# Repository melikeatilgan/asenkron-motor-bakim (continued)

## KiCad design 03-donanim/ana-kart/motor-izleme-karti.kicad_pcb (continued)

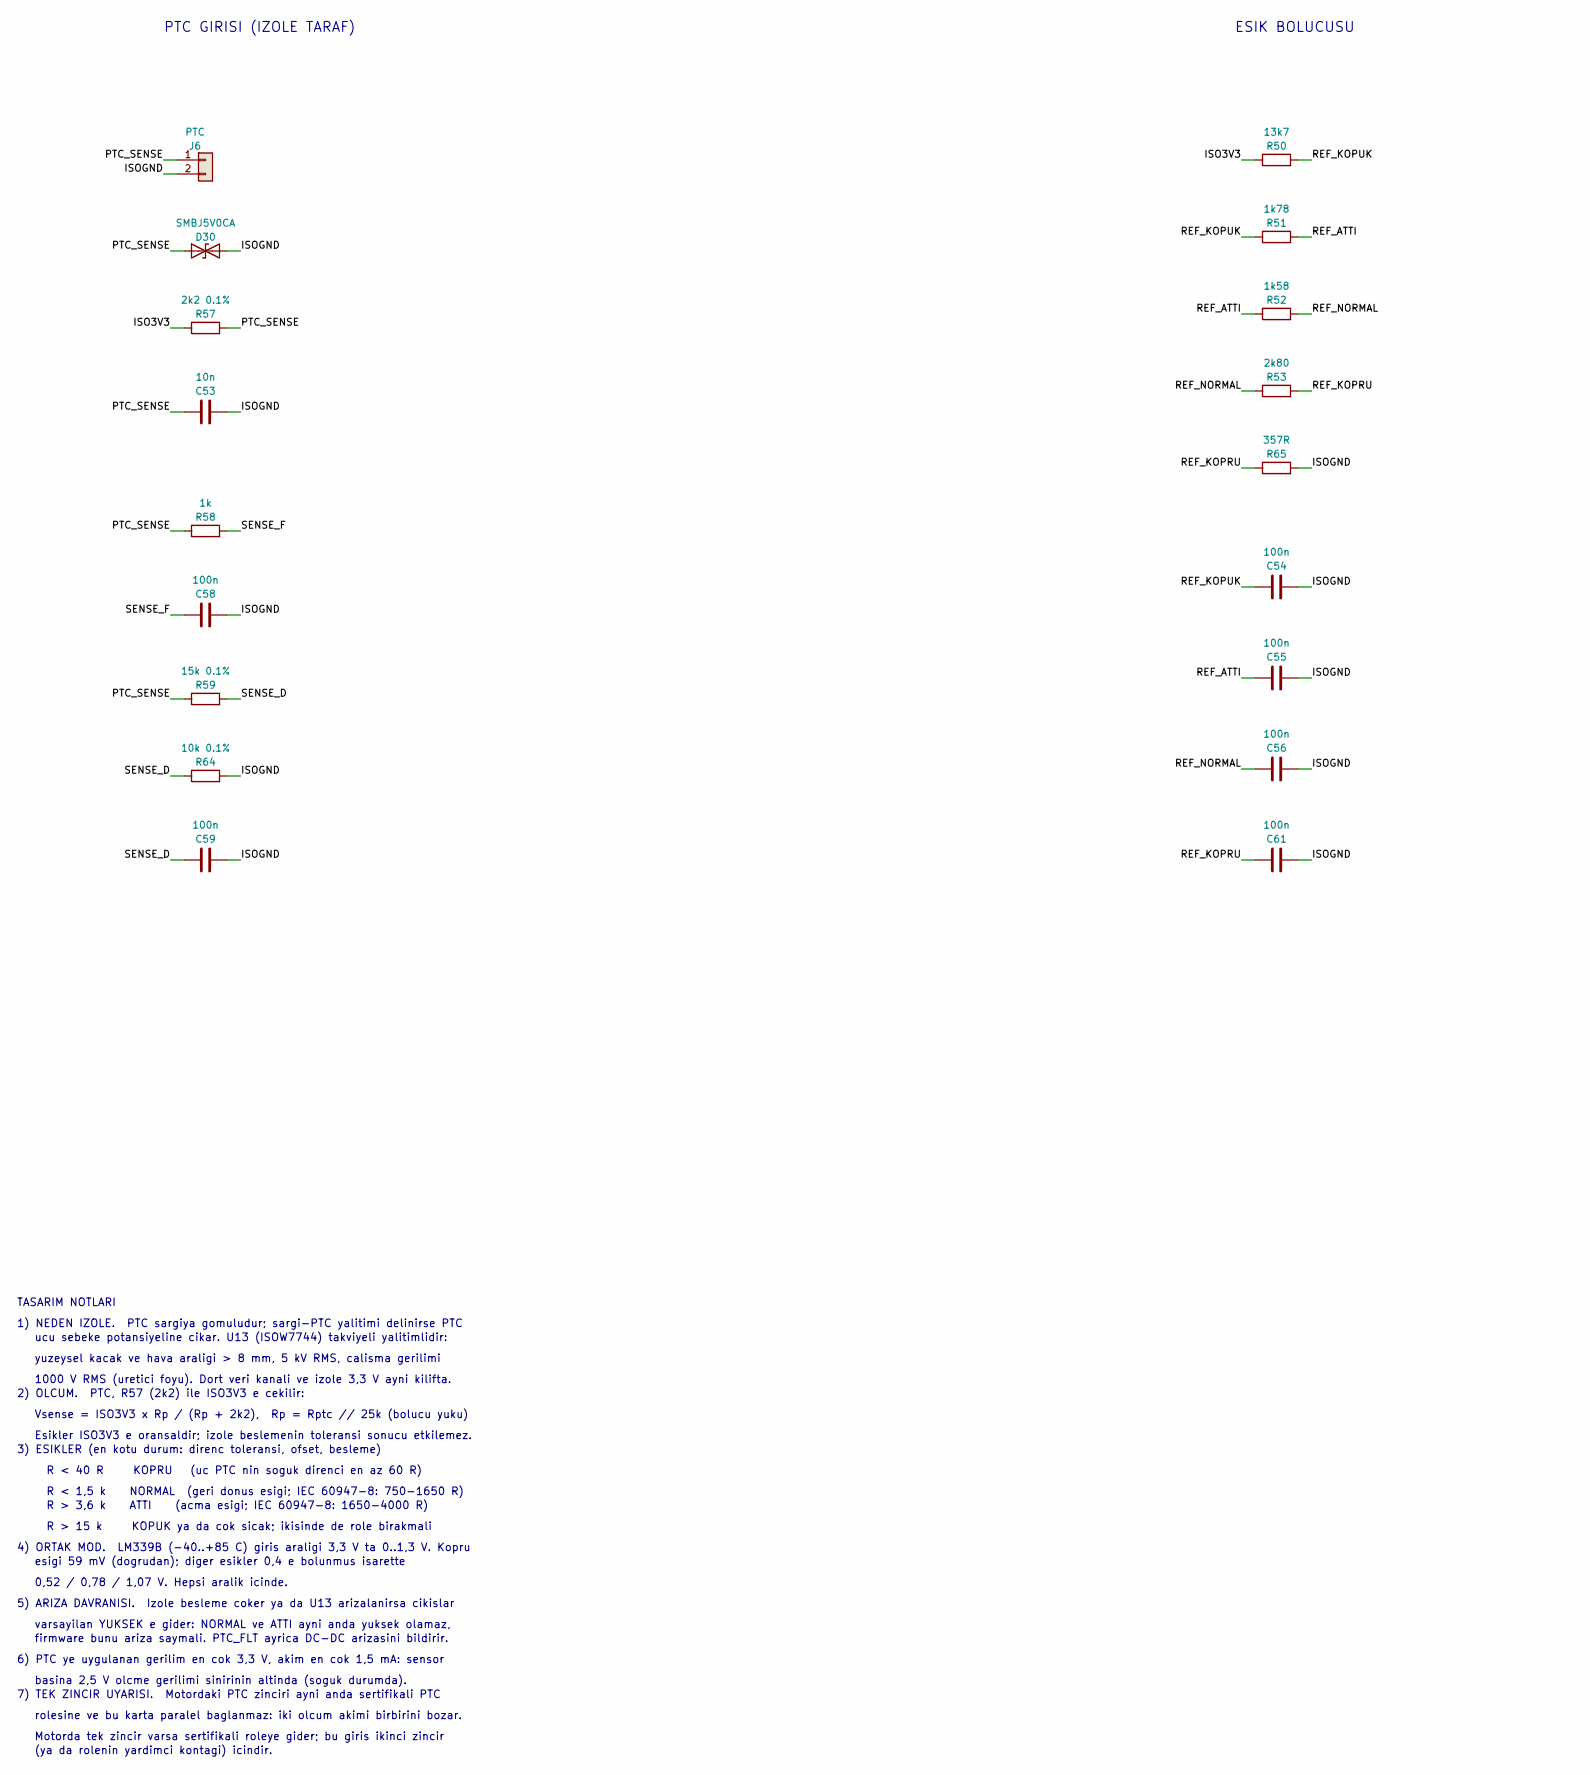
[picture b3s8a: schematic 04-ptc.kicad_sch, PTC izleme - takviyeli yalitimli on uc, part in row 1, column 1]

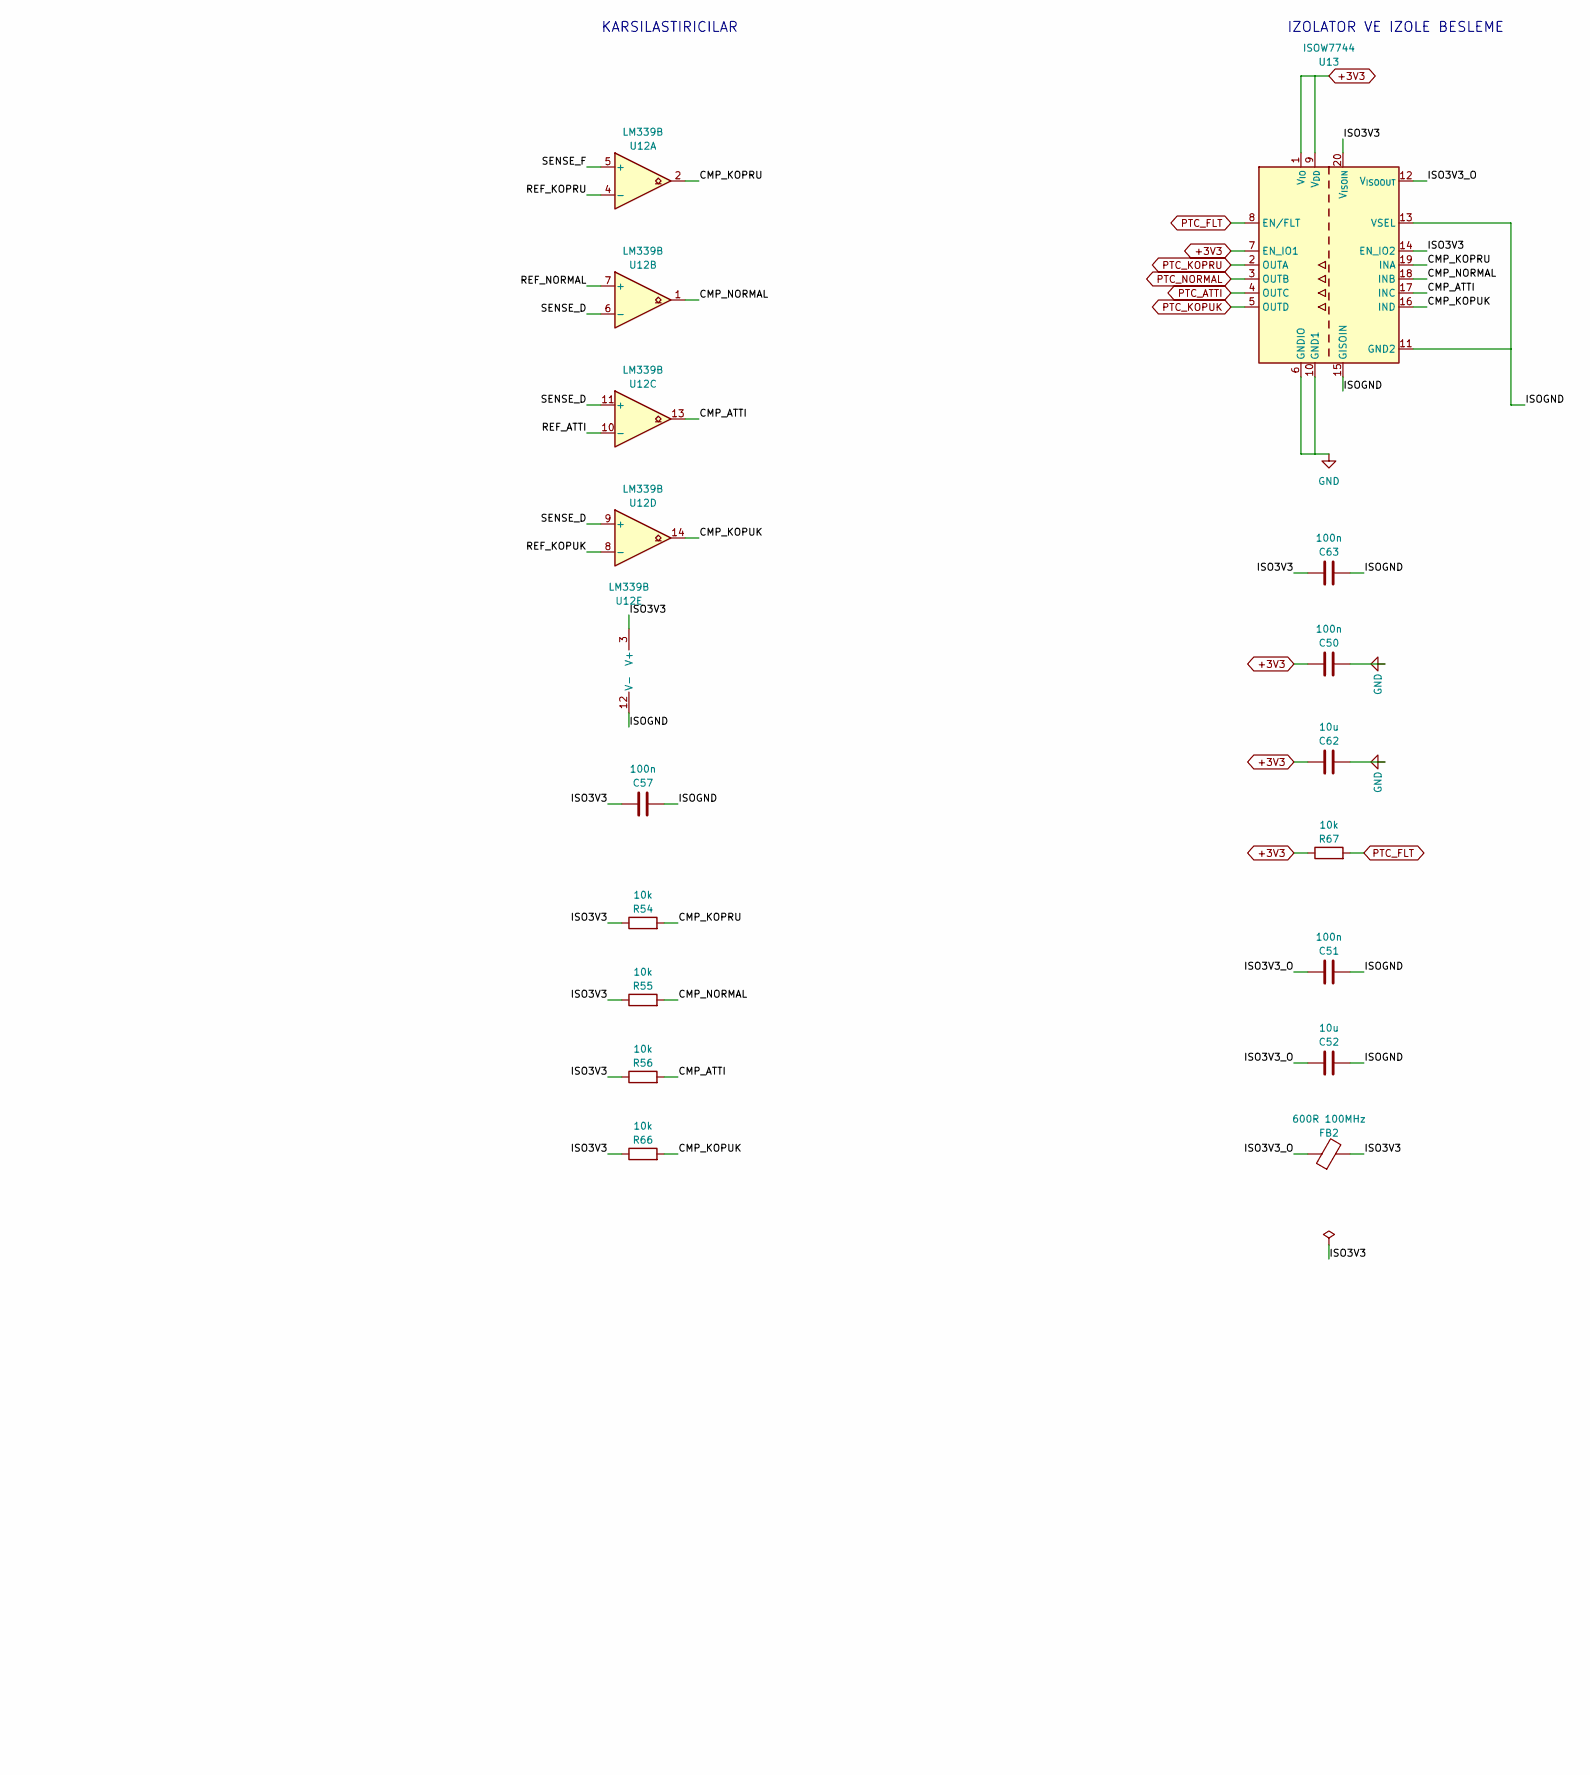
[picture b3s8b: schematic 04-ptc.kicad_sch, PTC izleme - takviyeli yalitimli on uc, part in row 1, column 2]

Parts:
C50, C51, C54, C55, C56, C57, C58, C59, C61, C63: 100n; C_0805_2012Metric
C52, C62: 10u; C_1206_3216Metric
C53: 10n; C_0805_2012Metric
D30: SMBJ5V0CA; D_SMB
FB2: 600R 100MHz; L_0805_2012Metric
J6: PTC; TerminalBlock_Phoenix_MPT-0,5-2-2.54_1x02_P2.54mm_Horizontal
R50: 13k7; R_0805_2012Metric
R51: 1k78; R_0805_2012Metric
R52: 1k58; R_0805_2012Metric
R53: 2k80; R_0805_2012Metric
R54, R55, R56, R66, R67: 10k; R_0805_2012Metric
R57: 2k2 0.1%; R_0805_2012Metric
R58: 1k; R_0805_2012Metric
R59: 15k 0.1%; R_0805_2012Metric
R64: 10k 0.1%; R_0805_2012Metric
R65: 357R; R_0805_2012Metric
U12: LM339B; SOIC-14_3.9x8.7mm_P1.27mm
U13: ISOW7744; SOIC-20W_7.5x12.8mm_P1.27mm_Ic8.1mm

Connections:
+3V3: C50.1, C62.1, R67.1, U13.1 (V_{IO}), U13.7 (EN_IO1), U13.9 (V_{DD}); also elsewhere on the board
/04-ptc/CMP_ATTI: R56.2, U12.13, U13.17 (INC)
/04-ptc/CMP_KOPRU: R54.2, U12.2, U13.19 (INA)
/04-ptc/CMP_KOPUK: R66.2, U12.14, U13.16 (IND)
/04-ptc/CMP_NORMAL: R55.2, U12.1, U13.18 (INB)
/04-ptc/ISO3V3: C57.1, C63.1, FB2.2, R50.1, R54.1, R55.1, R56.1, R57.1, R66.1, U12.3 (V+), U13.14 (EN_IO2), U13.20 (V_{ISOIN})
/04-ptc/ISO3V3_O: C51.1, C52.1, FB2.1, U13.12 (V_{ISOOUT})
/04-ptc/ISOGND: C51.2, C52.2, C53.2, C54.2, C55.2, C56.2, C57.2, C58.2, C59.2, C61.2, C63.2, D30.2 (A2), J6.2, R64.2, R65.2, U12.12 (V-), U13.11 (GND2), U13.13 (VSEL), U13.15 (GISOIN)
/04-ptc/PTC_SENSE: C53.1, D30.1 (A1), J6.1, R57.2, R58.1, R59.1
/04-ptc/REF_ATTI: C55.1, R51.2, R52.1, U12.10 (-)
/04-ptc/REF_KOPRU: C61.1, R53.2, R65.1, U12.4 (-)
/04-ptc/REF_KOPUK: C54.1, R50.2, R51.1, U12.8 (-)
/04-ptc/REF_NORMAL: C56.1, R52.2, R53.1, U12.7 (+)
/04-ptc/SENSE_D: C59.1, R59.2, R64.1, U12.6 (-), U12.9 (+), U12.11 (+)
/04-ptc/SENSE_F: C58.1, R58.2, U12.5 (+)
GND: C50.2, C62.2, U13.6 (GNDIO), U13.10 (GND1); also elsewhere on the board
PTC_ATTI: U13.4 (OUTC); also elsewhere on the board
PTC_FLT: R67.2, U13.8 (EN/FLT); also elsewhere on the board
PTC_KOPRU: U13.2 (OUTA); also elsewhere on the board
PTC_KOPUK: U13.5 (OUTD); also elsewhere on the board
PTC_NORMAL: U13.3 (OUTB); also elsewhere on the board

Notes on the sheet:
0,52 / 0,78 / 1,07 V. Hepsi aralik icinde.
yuzeysel kacak ve hava araligi > 8 mm, 5 kV RMS, calisma gerilimi
KARSILASTIRICILAR
varsayilan YUKSEK e gider: NORMAL ve ATTI ayni anda yuksek olamaz,
R < 40 R KOPRU (uc PTC nin soguk direnci en az 60 R)
5) ARIZA DAVRANISI. Izole besleme coker ya da U13 arizalanirsa cikislar
Motorda tek zincir varsa sertifikali roleye gider; bu giris ikinci zincir
firmware bunu ariza saymali. PTC_FLT ayrica DC-DC arizasini bildirir.
ESIK BOLUCUSU
R < 1,5 k NORMAL (geri donus esigi; IEC 60947-8: 750-1650 R)
R > 3,6 k ATTI (acma esigi; IEC 60947-8: 1650-4000 R)
2) OLCUM. PTC, R57 (2k2) ile ISO3V3 e cekilir:
6) PTC ye uygulanan gerilim en cok 3,3 V, akim en cok 1,5 mA: sensor
basina 2,5 V olcme gerilimi sinirinin altinda (soguk durumda).
PTC GIRISI (IZOLE TARAF)
(ya da rolenin yardimci kontagi) icindir.
TASARIM NOTLARI
R > 15 k KOPUK ya da cok sicak; ikisinde de role birakmali
1000 V RMS (uretici foyu). Dort veri kanali ve izole 3,3 V ayni kilifta.
esigi 59 mV (dogrudan); diger esikler 0,4 e bolunmus isarette
Vsense = ISO3V3 x Rp / (Rp + 2k2), Rp = Rptc // 25k (bolucu yuku)
7) TEK ZINCIR UYARISI. Motordaki PTC zinciri ayni anda sertifikali PTC
1) NEDEN IZOLE. PTC sargiya gomuludur; sargi-PTC yalitimi delinirse PTC
Esikler ISO3V3 e oransaldir; izole beslemenin toleransi sonucu etkilemez.
ucu sebeke potansiyeline cikar. U13 (ISOW7744) takviyeli yalitimlidir:
rolesine ve bu karta paralel baglanmaz: iki olcum akimi birbirini bozar.
3) ESIKLER (en kotu durum: direnc toleransi, ofset, besleme)
IZOLATOR VE IZOLE BESLEME
4) ORTAK MOD. LM339B (-40..+85 C) giris araligi 3,3 V ta 0..1,3 V. Kopru

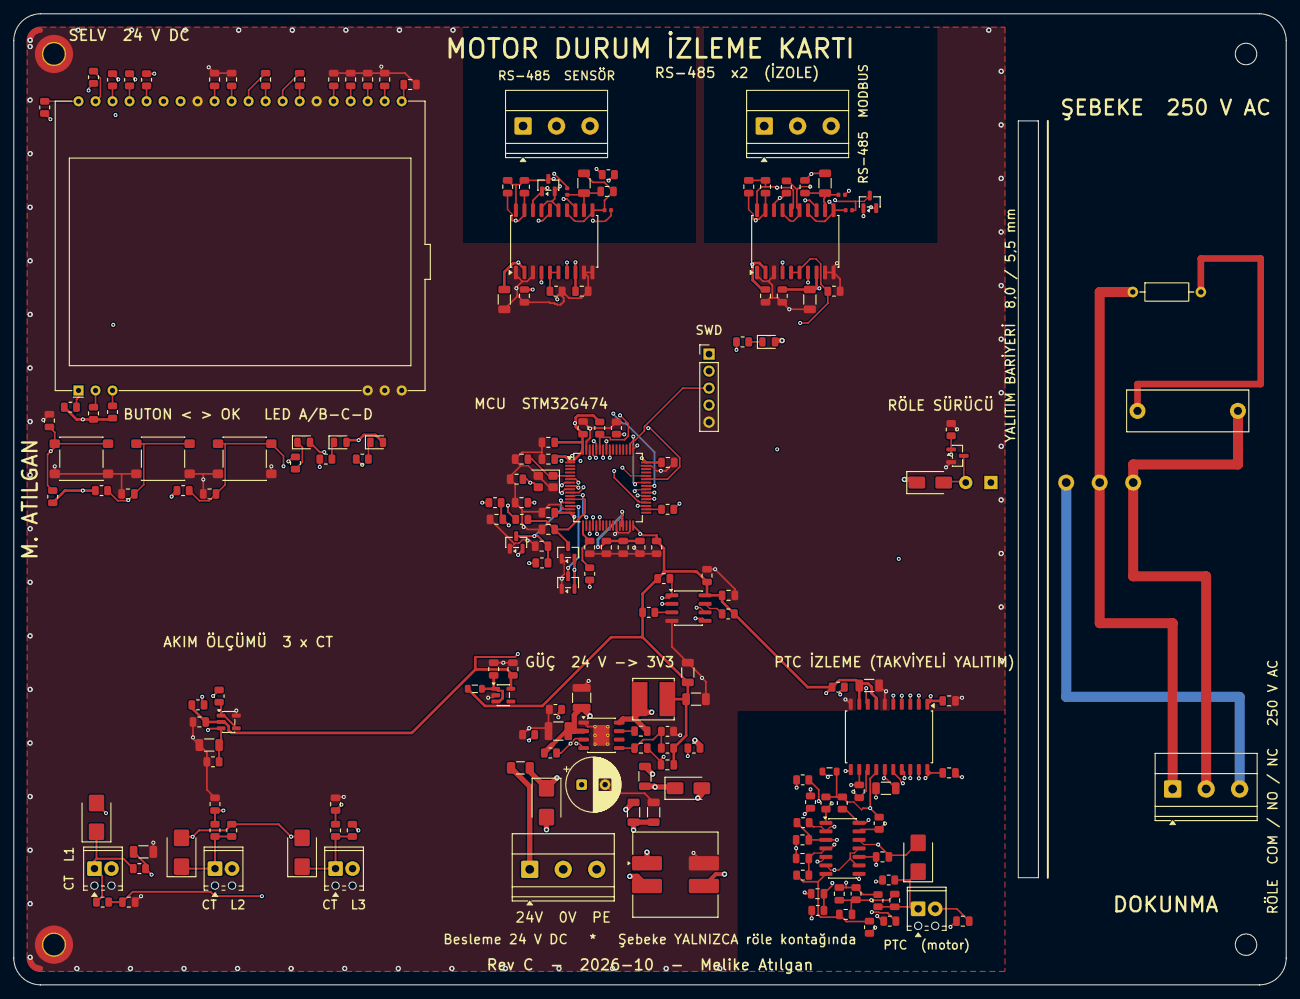
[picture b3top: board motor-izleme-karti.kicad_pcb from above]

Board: 4 copper layers, 190.0 x 145.0 mm, 191 parts (0 on the bottom side), 117 nets.

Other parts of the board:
MH1, MH3: MountingHole_3.2mm_M3_ISO7380_Pad_TopBottom
MH2, MH4: MountingHole_3.2mm_M3

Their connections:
GND: MH1.1, MH3.1; also elsewhere on the board

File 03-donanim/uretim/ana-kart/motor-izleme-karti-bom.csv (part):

"Refs","Value","Footprint","Qty","DNP"
"C1","470n 100V","Capacitor_SMD:C_1206_3216Metric","1",""
"C3","47u 63V","Capacitor_THT:CP_Radial_D8.0mm_P3.50mm","1",""
"C4","2u2 100V","Capacitor_SMD:C_1210_3225Metric","1",""
"C5","2u2 100V","Capacitor_SMD:C_1210_3225Metric","1",""
"C6","2n2 50V","Capacitor_SMD:C_0805_2012Metric","1",""
"C7","22u 10V","Capacitor_SMD:C_1206_3216Metric","1",""
"C8","22u 10V","Capacitor_SMD:C_1206_3216Metric","1",""
"C9","3n3","Capacitor_SMD:C_0805_2012Metric","1",""
"C10","330p","Capacitor_SMD:C_0805_2012Metric","1",""
"C12","15p C0G","Capacitor_SMD:C_0805_2012Metric","1",""
"C13","15p C0G","Capacitor_SMD:C_0805_2012Metric","1",""
"C14","1u","Capacitor_SMD:C_0805_2012Metric","1",""
"C15","1u","Capacitor_SMD:C_0805_2012Metric","1",""
"C20","100n","Capacitor_SMD:C_0805_2012Metric","1",""
"C21","100n","Capacitor_SMD:C_0805_2012Metric","1",""
"C22","100n","Capacitor_SMD:C_0805_2012Metric","1",""
"C23","100n","Capacitor_SMD:C_0805_2012Metric","1",""
"C24","1u","Capacitor_SMD:C_0805_2012Metric","1",""
"C25","100n","Capacitor_SMD:C_0805_2012Metric","1",""
"C26","100n","Capacitor_SMD:C_0805_2012Metric","1",""
"C27","100n","Capacitor_SMD:C_0805_2012Metric","1",""
"C28","100n","Capacitor_SMD:C_0805_2012Metric","1",""
"C29","4u7","Capacitor_SMD:C_0805_2012Metric","1",""
"C30","10u","Capacitor_SMD:C_1206_3216Metric","1",""
"C31","100n","Capacitor_SMD:C_0805_2012Metric","1",""
"C32","10u","Capacitor_SMD:C_1206_3216Metric","1",""
"C33","100n","Capacitor_SMD:C_0805_2012Metric","1",""
"C35","100n","Capacitor_SMD:C_0805_2012Metric","1",""
"C36","100n","Capacitor_SMD:C_0805_2012Metric","1",""
"C37","100n","Capacitor_SMD:C_0805_2012Metric","1",""
"C38","47n","Capacitor_SMD:C_0805_2012Metric","1",""
"C39","47n","Capacitor_SMD:C_0805_2012Metric","1",""
"C40","47n","Capacitor_SMD:C_0805_2012Metric","1",""
"C50","100n","Capacitor_SMD:C_0805_2012Metric","1",""
"C51","100n","Capacitor_SMD:C_0805_2012Metric","1",""
"C52","10u","Capacitor_SMD:C_1206_3216Metric","1",""
"C53","10n","Capacitor_SMD:C_0805_2012Metric","1",""
"C54","100n","Capacitor_SMD:C_0805_2012Metric","1",""
"C55","100n","Capacitor_SMD:C_0805_2012Metric","1",""
"C56","100n","Capacitor_SMD:C_0805_2012Metric","1",""
"C57","100n","Capacitor_SMD:C_0805_2012Metric","1",""
"C58","100n","Capacitor_SMD:C_0805_2012Metric","1",""
"C59","100n","Capacitor_SMD:C_0805_2012Metric","1",""
"C60","100n X2 275VAC R46KI310000M1M","Capacitor_THT:C_Rect_L18.0mm_W6.0mm_P15.00mm_FKS3_FKP3","1","Monte Etme"
"C61","100n","Capacitor_SMD:C_0805_2012Metric","1",""
"C62","10u","Capacitor_SMD:C_1206_3216Metric","1",""
"C63","100n","Capacitor_SMD:C_0805_2012Metric","1",""
"C70","1u 25V","Capacitor_SMD:C_0805_2012Metric","1",""
"C71","1u 25V","Capacitor_SMD:C_0805_2012Metric","1",""
"C72","1u 25V","Capacitor_SMD:C_0805_2012Metric","1",""
"C73","1u 25V","Capacitor_SMD:C_0805_2012Metric","1",""
"C74","1u 25V","Capacitor_SMD:C_0805_2012Metric","1",""
"C75","1u 25V","Capacitor_SMD:C_0805_2012Metric","1",""
"C76","1u 25V","Capacitor_SMD:C_0805_2012Metric","1",""
"C77","1u 25V","Capacitor_SMD:C_0805_2012Metric","1",""
"C78","1u 25V","Capacitor_SMD:C_0805_2012Metric","1",""
"C79","1u","Capacitor_SMD:C_0805_2012Metric","1",""
"C80","100n","Capacitor_SMD:C_0805_2012Metric","1",""
"C81","100n","Capacitor_SMD:C_0805_2012Metric","1",""
"C82","100n","Capacitor_SMD:C_0805_2012Metric","1",""
"C85","100n","Capacitor_SMD:C_0805_2012Metric","1",""
"C86","10n","Capacitor_SMD:C_0805_2012Metric","1",""
"C87","100n","Capacitor_SMD:C_0805_2012Metric","1",""
"C88","10u","Capacitor_SMD:C_1206_3216Metric","1",""
"C89","10n","Capacitor_SMD:C_0805_2012Metric","1",""
"C90","100n","Capacitor_SMD:C_0805_2012Metric","1",""
"C91","10u","Capacitor_SMD:C_1206_3216Metric","1",""
"C92","100n","Capacitor_SMD:C_0805_2012Metric","1",""
"C93","100n","Capacitor_SMD:C_0805_2012Metric","1",""
"C94","100n","Capacitor_SMD:C_0805_2012Metric","1",""
"C95","10u","Capacitor_SMD:C_1206_3216Metric","1",""
"C96","100n","Capacitor_SMD:C_0805_2012Metric","1",""
"C97","100n","Capacitor_SMD:C_0805_2012Metric","1",""
"C98","10u","Capacitor_SMD:C_1206_3216Metric","1",""
"C99","100n","Capacitor_SMD:C_0805_2012Metric","1",""
"CY1","2n2 2kV","Capacitor_SMD:C_1206_3216Metric","1",""
"CY2","2n2 2kV","Capacitor_SMD:C_1206_3216Metric","1",""
"D1","SMBJ33CA","Diode_SMD:D_SMB","1",""
"D2","SS110","Diode_SMD:D_SMA","1",""
"D11","SMBJ5V0CA","Diode_SMD:D_SMB","1",""
"D12","SMBJ5V0CA","Diode_SMD:D_SMB","1",""
"D13","SMBJ5V0CA","Diode_SMD:D_SMB","1",""
"D21","BAT54S","Package_TO_SOT_SMD:SOT-23","1",""
"D22","BAT54S","Package_TO_SOT_SMD:SOT-23","1",""
"D23","BAT54S","Package_TO_SOT_SMD:SOT-23","1",""
"D30","SMBJ5V0CA","Diode_SMD:D_SMB","1",""
"D40","SS110","Diode_SMD:D_SMA","1",""
"D41","Role durumu","LED_SMD:LED_0805_2012Metric","1",""
"D50","Yesil A/B","LED_SMD:LED_0805_2012Metric","1",""
"D51","Sari C","LED_SMD:LED_0805_2012Metric","1",""
"D52","Kirmizi D","LED_SMD:LED_0805_2012Metric","1",""
"D90","SM712","Package_TO_SOT_SMD:SOT-23","1",""
"D94","SM712","Package_TO_SOT_SMD:SOT-23","1",""
"DS1","EA DOGM128W-6 + LED55X46-A","Display:EA_DOGM128-6","1",""
"F1","1A T 63V 0468001.NR","Fuse:Fuse_1206_3216Metric","1",""
"FB1","600R 100MHz","Inductor_SMD:L_0805_2012Metric","1",""
"FB2","600R 100MHz","Inductor_SMD:L_0805_2012Metric","1",""
"FB3","BLM15HD182SN1D","Inductor_SMD:L_0402_1005Metric","1",""
"FB4","BLM15HD182SN1D","Inductor_SMD:L_0402_1005Metric","1",""
"FB5","BLM15HD182SN1D","Inductor_SMD:L_0402_1005Metric","1",""
"FB6","BLM15HD182SN1D","Inductor_SMD:L_0402_1005Metric","1",""
"J1","24 VDC + PE","TerminalBlock_Phoenix:TerminalBlock_Phoenix_MKDS-1,5-3_1x03_P5.00mm_Horizontal","1",""
"J2","SWD","Connector_PinHeader_2.54mm:PinHeader_1x05_P2.54mm_Vertical","1",""
"J3","CT L1","TerminalBlock_Phoenix:TerminalBlock_Phoenix_MPT-0,5-2-2.54_1x02_P2.54mm_Horizontal","1",""
"J4","CT L2","TerminalBlock_Phoenix:TerminalBlock_Phoenix_MPT-0,5-2-2.54_1x02_P2.54mm_Horizontal","1",""
"J5","CT L3","TerminalBlock_Phoenix:TerminalBlock_Phoenix_MPT-0,5-2-2.54_1x02_P2.54mm_Horizontal","1",""
"J6","PTC","TerminalBlock_Phoenix:TerminalBlock_Phoenix_MPT-0,5-2-2.54_1x02_P2.54mm_Horizontal","1",""
"J7","Kumanda devresi","TerminalBlock_Phoenix:TerminalBlock_Phoenix_MKDS-1,5-3_1x03_P5.00mm_Horizontal","1",""
"J8","SENSOR BASLIGI HATTI","TerminalBlock_Phoenix:TerminalBlock_Phoenix_MKDS-1,5-3_1x03_P5.00mm_Horizontal","1",""
"J9","MODBUS RTU (SCADA)","TerminalBlock_Phoenix:TerminalBlock_Phoenix_MKDS-1,5-3_1x03_P5.00mm_Horizontal","1",""
"K1","FINDER 34.51 / 24 VDC","motor-izleme:Relay_SPDT_Finder_34.51_Vertical_Fab","1",""
"L1","SRF1260-101M","Inductor_SMD:L_CommonModeChoke_Bourns_SRF1260","1",""
"L2","33uH SRN6045TA-330M","Inductor_SMD:L_Bourns_SRN6045TA","1",""
"Q10","2N7002BK","Package_TO_SOT_SMD:SOT-23","1",""
"R2","80k6","Resistor_SMD:R_0805_2012Metric","1",""
"R3","49k9","Resistor_SMD:R_0805_2012Metric","1",""
"R4","499k","Resistor_SMD:R_0805_2012Metric","1",""
"R5","48k7","Resistor_SMD:R_0805_2012Metric","1",""
"R6","27k4","Resistor_SMD:R_0805_2012Metric","1",""
"R7","143k","Resistor_SMD:R_0805_2012Metric","1",""
"R10","10k","Resistor_SMD:R_0805_2012Metric","1",""
"R20","10k","Resistor_SMD:R_0805_2012Metric","1",""
"R21","10k","Resistor_SMD:R_0805_2012Metric","1",""
"R22","1k","Resistor_SMD:R_0805_2012Metric","1",""
"R23","100R","Resistor_SMD:R_0805_2012Metric","1",""
"R31","1k","Resistor_SMD:R_0805_2012Metric","1",""
"R32","1k","Resistor_SMD:R_0805_2012Metric","1",""
"R33","1k","Resistor_SMD:R_0805_2012Metric","1",""
"R41","1k","Resistor_SMD:R_0805_2012Metric","1",""
"R42","1k","Resistor_SMD:R_0805_2012Metric","1",""
"R43","1k","Resistor_SMD:R_0805_2012Metric","1",""
"R50","13k7","Resistor_SMD:R_0805_2012Metric","1",""
"R51","1k78","Resistor_SMD:R_0805_2012Metric","1",""
"R52","1k58","Resistor_SMD:R_0805_2012Metric","1",""
"R53","2k80","Resistor_SMD:R_0805_2012Metric","1",""
"R54","10k","Resistor_SMD:R_0805_2012Metric","1",""
"R55","10k","Resistor_SMD:R_0805_2012Metric","1",""
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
